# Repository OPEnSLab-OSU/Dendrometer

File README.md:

<p align="center">
    
  </a>
</p>

<h3 align="center">Dendrometer</h3>

## Introduction
The Dendrometer is an ongoing project that strives to enable ecological researchers and/or care-takers of grape plants to be able to effectively measure diurnal fluctuations in grape vines. Such information can be crucial for producing market-ideal grapes, as the shrinkage and growth of the vines are important indicators of when the plant is in need of water. Learn more about the design and outcomes on our <a href="https://github.com/OPEnSLab-OSU/OPEnS-Lab-Home/wiki/Dendrometer">Dendrometer Lab Wiki</a>. 

## Key Features
  - Data is collected and written to a SD card every 15 minutes, allowing the system to operate for long durations without human intervention
  - Devices can wirelessly report data back to a remote server by communicating with an internet-connected "hub" device
  - Magnetic encoder ([AS5311](https://ams.com/documents/20143/36005/AS5311_DS000200_2-00.pdf)) has a resolution of ~488nm with an extremely low temperature dependency (ideal for outdoor use)
  - Integration with [Loom](https://github.com/OPEnSLab-OSU/Loom-V4), which will allow this device to support plug-and-play functionalities with integrated sensors

## Directory 
### PCB: 
Printed circuit board (PCB) design files for the nodes. 
### src: 
Contains all of the code used on the dendrometer.
LoRa: Contains the source code for the node sensors and the LTE hub. This uses LoRa batch uploading which will upload all of the collected data at set intervals.
LoRa Non Batch: Contains the source code for the node sensors and the LTE hub. This will only upload ONE packet of data at set intervals. All of the data is still saved on SD card.
WiFi: Contains the source code for the WiFi connected nodes.

## Relevant Documents
* [User Manual](https://docs.google.com/document/d/1OHKa2jYamG2kPEfxrQMzi3MNHZGgkPIG/)
* [HardwareX Paper](https://www.sciencedirect.com/science/article/pii/S246806722100078X)
* [Troubleshooting Guide](https://docs.google.com/document/d/1E4zUMmSh5PVmP7RXUqQrh7S9IGuxQKPj5EQ5KcT2HYE/edit?usp=sharing)
* [Mechanical Assembly Guide](https://docs.google.com/document/d/1LzM_XnqVP9GkIqY2_pnTvdrFFe5u78ZPXJizvT70y4o/edit?usp=sharing)
* [Electronics Assembly Guide](https://docs.google.com/document/d/1BaNuNSJrL86lxKixB8chgZGySgj0bhYSMtVzJu6EDW4/edit?usp=sharing)
* [MongoDB Dashboard Guide](https://docs.google.com/document/d/1PlT9hrC62OXXhL8AD17e3FiPCwlHFJaZIvXCRnmihIE/edit?usp=sharing)
* [Installation Guide (Outdated)](https://docs.google.com/document/d/1GR2qeMWASApCwk-RbZwvsvWmB1qEz0QU8RcxwjgoDQY/edit?usp=sharing)

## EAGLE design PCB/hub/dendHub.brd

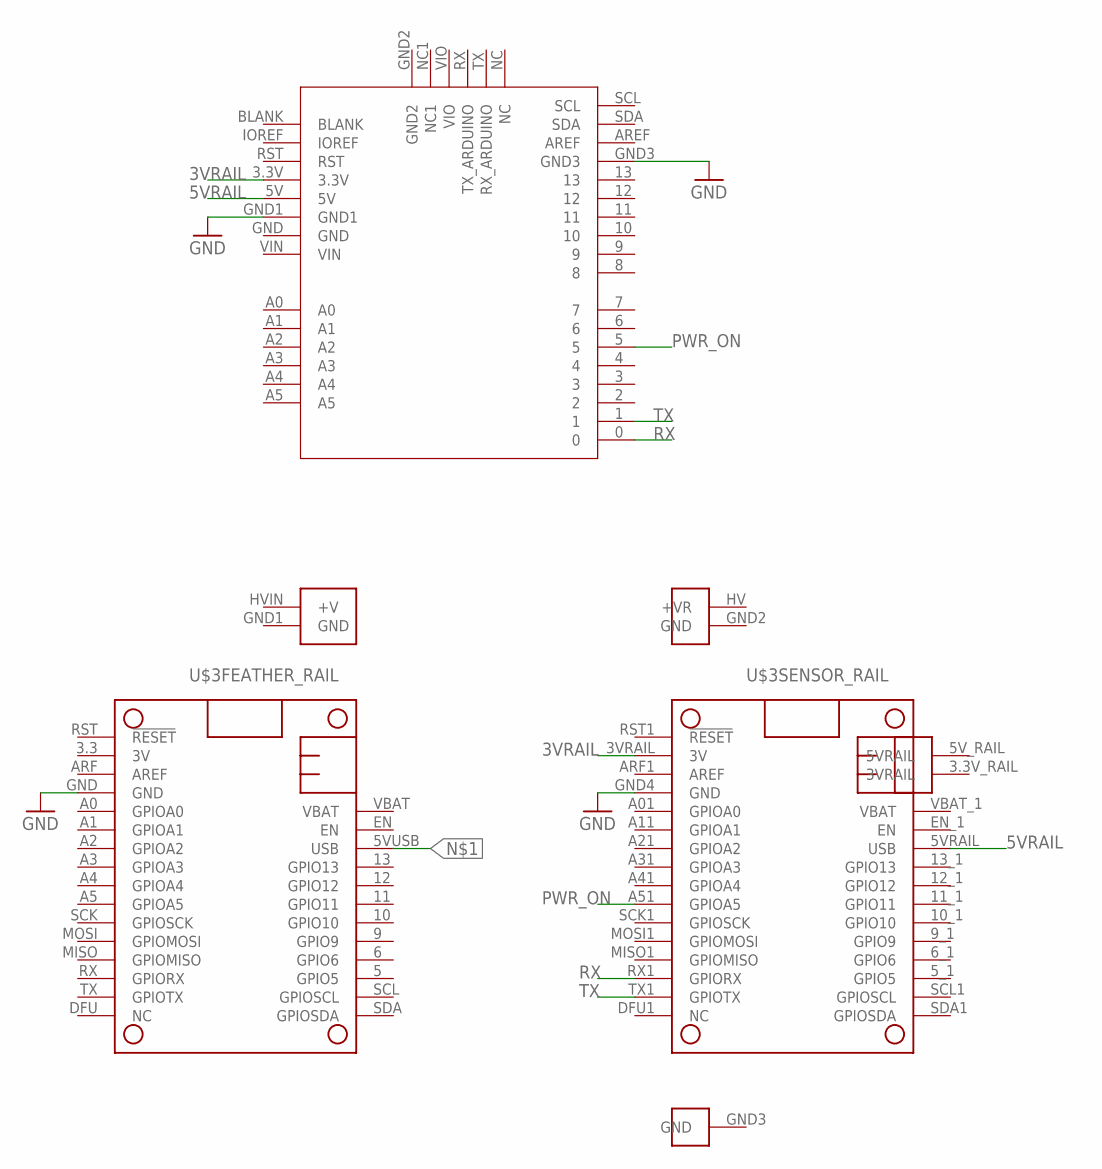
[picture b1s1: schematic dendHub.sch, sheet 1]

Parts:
U$1: LTE_BOARD; LTE_BOARD_FOOTPRINT
U$3: HYPNOS_V3

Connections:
3VRAIL: U$1.3.3V, U$3.3VRAIL (3V)
5VRAIL: U$1.5V, U$3.5VRAIL (USB)
GND: U$1.GND1, U$1.GND3, U$3.GND, U$3.GND4 (GND); also elsewhere on the board
unnamed 3: U$3.5VUSB (USB); also elsewhere on the board
PWR_ON: U$1.5, U$3.A51 (GPIOA5)
RX: U$1.0, U$3.RX1 (GPIORX)
TX: U$1.1, U$3.TX1 (GPIOTX)

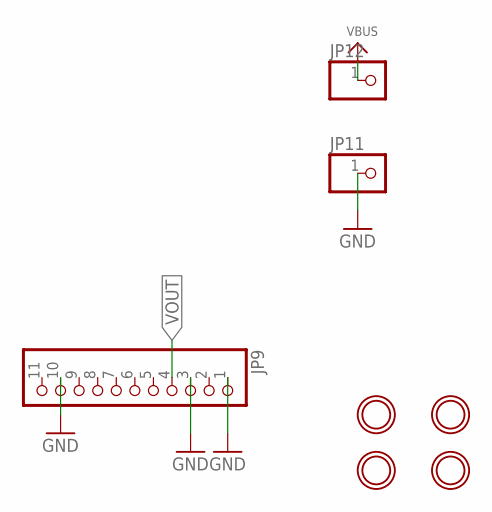
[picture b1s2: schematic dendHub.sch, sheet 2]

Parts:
JP9: HEADER-1X1176MIL; 1X11_ROUND_76
JP11, JP12: HEADER-1X1; 1X01_OVAL
U$45, U$46, U$47, U$48: MOUNTINGHOLE2.5; MOUNTINGHOLE_2.5_PLATED

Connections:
GND: JP9.1, JP9.3, JP9.10, JP11.1; also elsewhere on the board
VBUS: JP12.1
VOUT: JP9.4; also elsewhere on the board

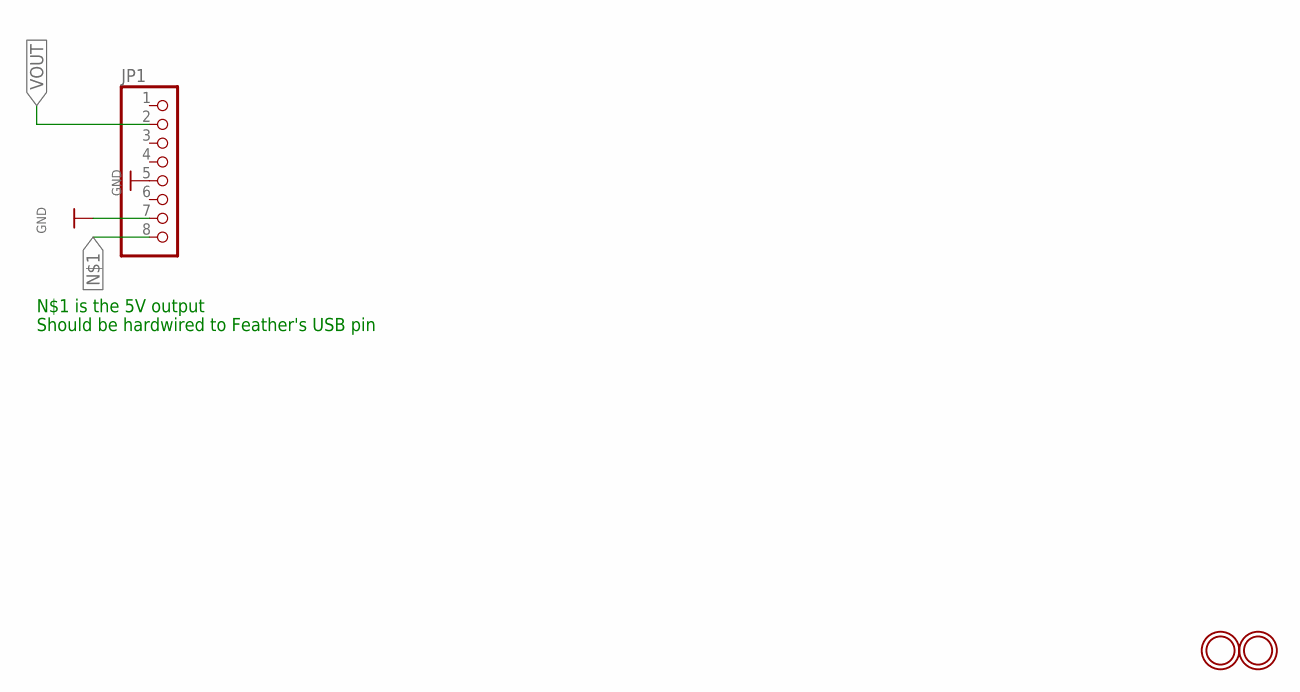
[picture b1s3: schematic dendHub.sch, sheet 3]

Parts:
JP1: HEADER-1X8ROUND; 1X08_ROUND
U$56, U$57: MOUNTINGHOLE2.5; MOUNTINGHOLE_2.5_PLATED

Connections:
GND: JP1.5, JP1.7; also elsewhere on the board
unnamed 3: JP1.8; also elsewhere on the board
VOUT: JP1.2; also elsewhere on the board

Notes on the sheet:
N$1 is the 5V output
Should be hardwired to Feather's USB pin

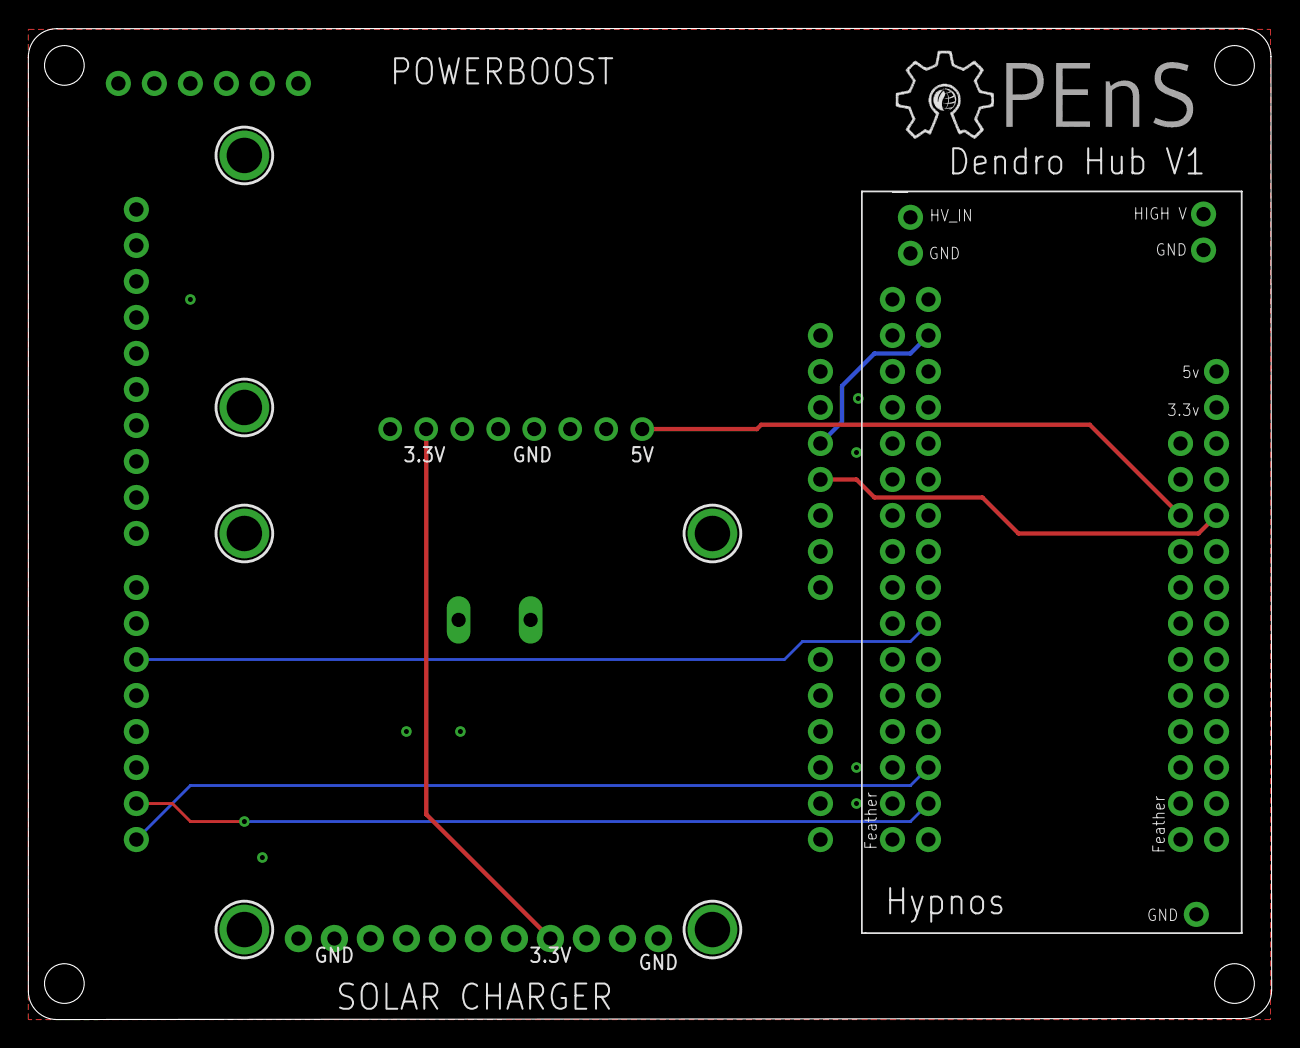
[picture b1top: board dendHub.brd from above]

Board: 2 copper layers, 87.7 x 69.9 mm, 13 parts (1 on the bottom side), 8 nets.

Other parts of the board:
U$2: OPENS-LOGO

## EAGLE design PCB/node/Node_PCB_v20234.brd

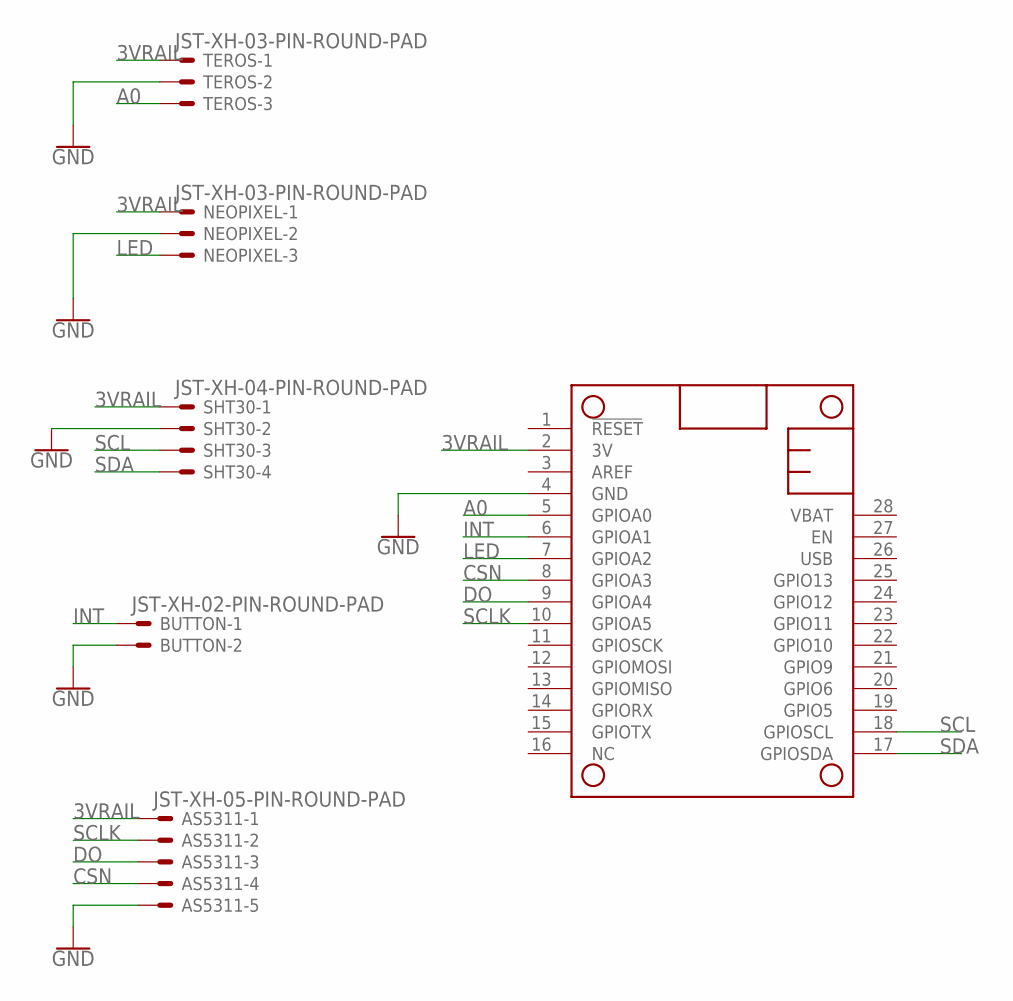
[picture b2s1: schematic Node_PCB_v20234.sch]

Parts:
AS5311: JST-XH-05-PIN-ROUND-PAD; JST-XH-05-PACKAGE-ROUND-PAD
BUTTON: JST-XH-02-PIN-ROUND-PAD; JST-XH-02-PACKAGE-ROUND-PAD
MS1: FEATHERWING
NEOPIXEL: JST-XH-03-PIN-ROUND-PAD; JST-XH-03-PACKAGE-ROUND-PAD
SHT30: JST-XH-04-PIN-ROUND-PAD; JST-XH-04-PACKAGE-ROUND-PAD
TEROS: JST-XH-03-PIN-ROUND-PAD; JST-XH-03-PACKAGE-ROUND-PAD

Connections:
3VRAIL: AS5311.1, MS1.2 (3V), NEOPIXEL.1, SHT30.1, TEROS.1
A0: MS1.5 (GPIOA0), TEROS.3
CSN: AS5311.4, MS1.8 (GPIOA3)
DO: AS5311.3, MS1.9 (GPIOA4)
GND: AS5311.5, BUTTON.2, MS1.4 (GND), NEOPIXEL.2, SHT30.2, TEROS.2
INT: BUTTON.1, MS1.6 (GPIOA1)
LED: MS1.7 (GPIOA2), NEOPIXEL.3
SCL: MS1.18 (GPIOSCL), SHT30.3
SCLK: AS5311.2, MS1.10 (GPIOA5)
SDA: MS1.17 (GPIOSDA), SHT30.4

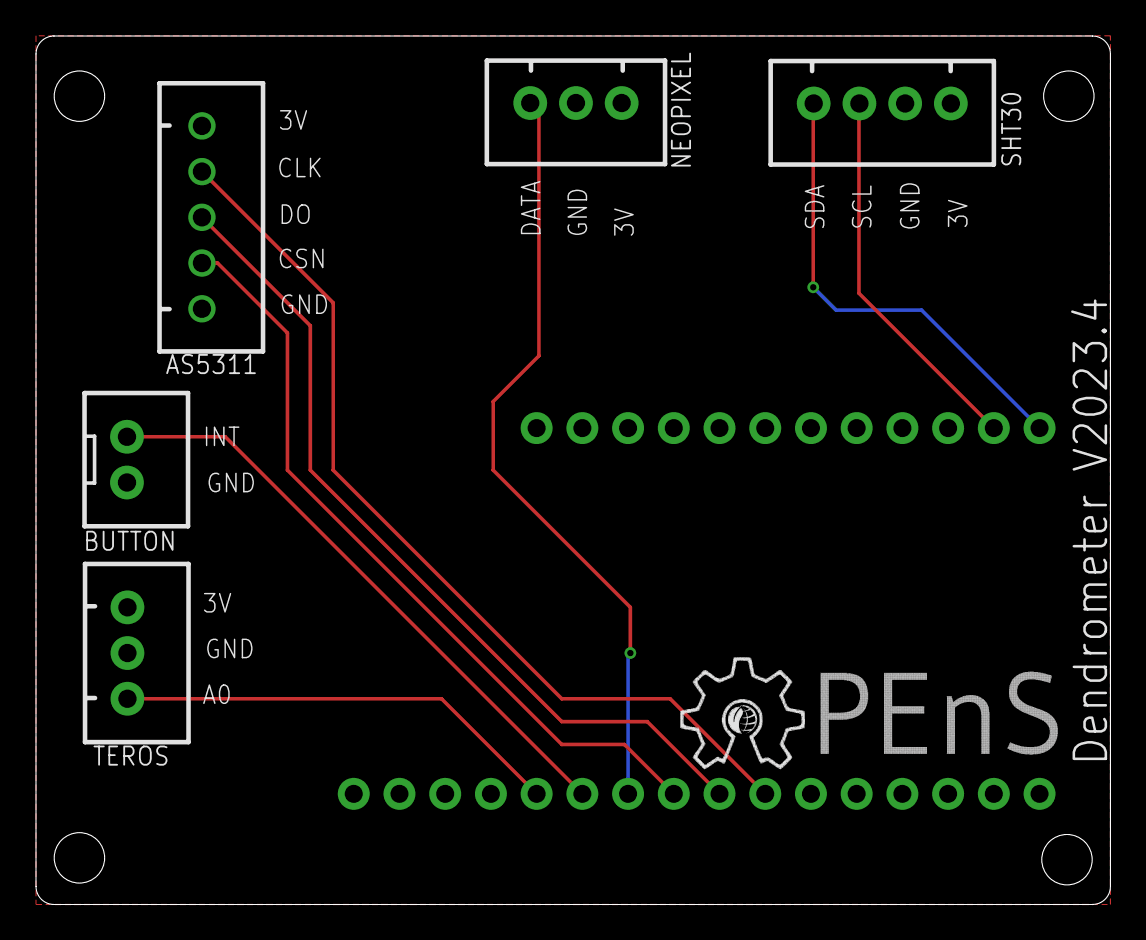
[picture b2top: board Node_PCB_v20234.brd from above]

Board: 2 copper layers, 59.7 x 48.2 mm, 7 parts (0 on the bottom side), 10 nets.

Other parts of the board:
U$1: OPENS-LOGO

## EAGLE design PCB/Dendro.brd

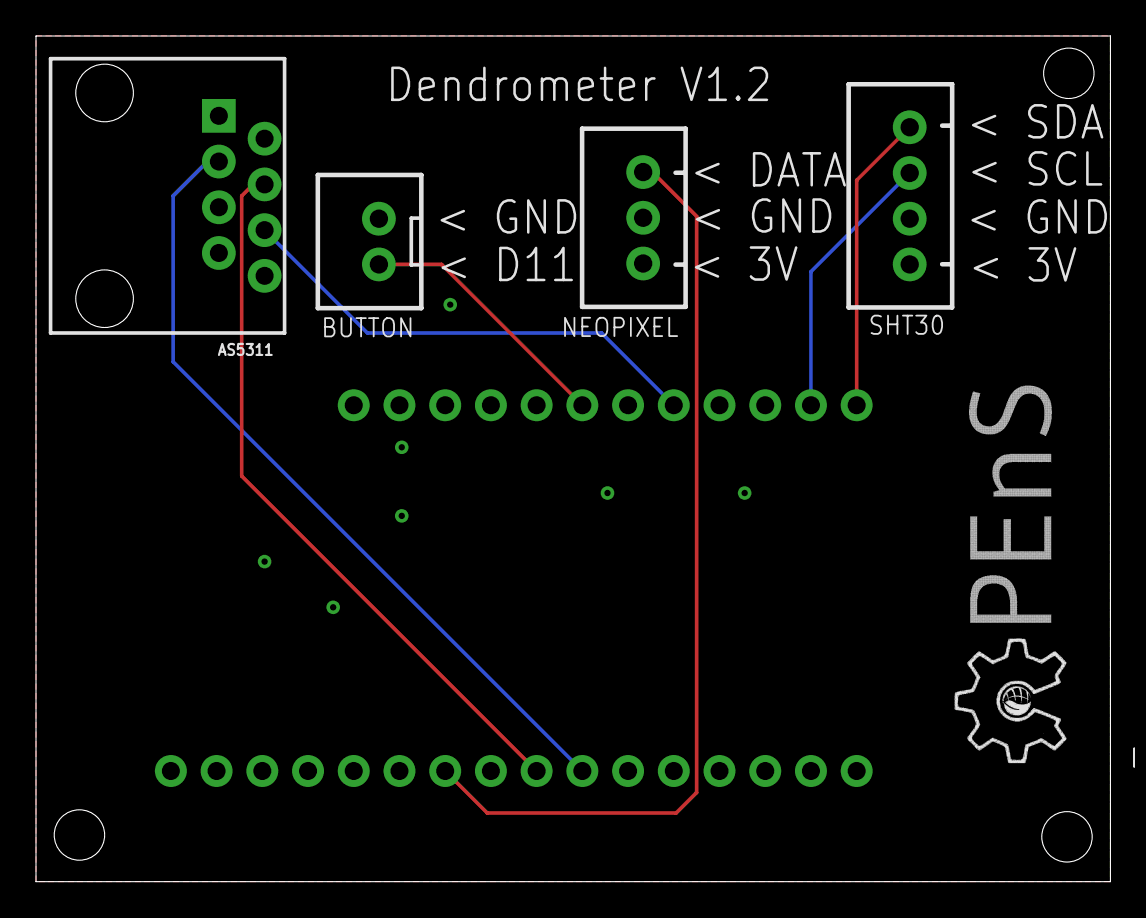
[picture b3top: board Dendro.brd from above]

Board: 2 copper layers, 59.7 x 47.0 mm, 6 parts (0 on the bottom side), 9 nets.

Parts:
AS5311: RJ45; RJ45-8
BUTTON: JST-XH-02-PIN-ROUND-PAD; JST-XH-02-PACKAGE-ROUND-PAD
MS1: FEATHERWING
NEOPIXEL: JST-XH-03-PIN-ROUND-PAD; JST-XH-03-PACKAGE-ROUND-PAD
SHT30: JST-XH-04-PIN-ROUND-PAD; JST-XH-04-PACKAGE-ROUND-PAD
U$1: OPENS-LOGO

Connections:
3VRAIL: AS5311.1, AS5311.2, MS1.2, NEOPIXEL.1, SHT30.1
A2: MS1.7, NEOPIXEL.3
CSN: AS5311.6, MS1.21
D11: BUTTON.1, MS1.23
DO: AS5311.4, MS1.9
GND: AS5311.5, BUTTON.2, MS1.4, NEOPIXEL.2, SHT30.2
SCL: MS1.18, SHT30.3
SCLK: AS5311.3, MS1.10
SDA: MS1.17, SHT30.4

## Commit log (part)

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2019-07-12 Create Linear_Slide_4.ino
    Reads sensor data and stores on micro SD using Adalogger and RTC
2019-08-22 SHT and Voltage ref
    Added sht sensor, lm4040 voltage reference
2019-11-04 image and image folder
2019-11-05 another picture
2019-11-05 picture and drawing
2019-11-05 graph
2019-11-25 Added AS5311, AS5311 example, and updates potentiometer
2019-11-25 Most recent linear potentiometer code
2019-11-25 Loom
2019-12-09 Create test
2019-12-21 Connected to Wifi
2019-12-22 Successfully got PWM
2019-12-24 Implemented basic HTTP Functionality
2019-12-26 Successfully made PUT request
2019-12-29 Implemented basic functionality of writing
2019-12-29 Implemented vector functionality for update
2019-12-30 Implemented functionality of refresh
2019-12-30 Added example of GSheets usage
2019-12-30 Removed extra delay
2020-01-07 Removed extra files
2020-01-13 Integrated WiFi onto Feather M0
2020-01-27 Before integrating Serial
2020-01-29 Integrated Serial
2020-01-29 Attempt to fix wifi and added 16 loop
2020-01-30 Added Wifi Disconnect statement
2020-02-24 Successfully sensed rollover
2020-02-25 Displacement algorithm v1
2020-02-26 Remove .DS_STORE
2020-02-26 File Reorg
2020-03-05 Integrated basic Loom functionality, need to parse data
2020-03-10 Added Loom SD and refactored AS5331
2020-03-11 Refactored Code into header files and renamed file typo
2020-03-12 Integrated SD card functionality
2020-04-23 Added mechanical test code
2020-06-07 Push code for summer mechanical testing
2020-07-20 Renamed Hypnos variables
2020-08-11 Updated summer prototyping code
2020-08-30 Updated summer code testing
2020-08-30 Updated code for summer testing
2020-09-07 Added error checking for magnet position
2020-09-22 Changed time between readings to 15 minutes
2020-09-23 Added temporary magnet checker during setup
2020-10-02 Magnet checker during setup implemented
2020-10-10 Neopixel added, more specific error messages
2020-10-10 More detailed error messages for testing
2020-10-12 Warm up time added for AS5311, Neopixel blink
2020-11-07 Create STLfiles
2020-11-10 Testing New Schematic Editor
2020-11-10 Updated Schematic for AGU
2020-11-13 Battery levels recorded
2020-12-06 Dendrometer PCB V1
2020-12-06 PCB PDFs
2020-12-06 Rename DendroSchem.brd to Dendro.brd
2020-12-06 Rename DendroSchem.sch to Dendro.sch
2020-12-11 Added RTC PST timing and decreased LED time
2021-01-07 Added interrupt button
2021-01-12 Create dwgs
2021-01-12 Create boop
2021-01-12 Create go
2021-01-12 Create kip
2021-01-24 Zenodo file uploaded
2021-01-27 Cleaned up code
2021-01-29 Neopixel Interrupt
2021-01-30 Neopixel indicator
2021-01-30 RTC Update
2021-01-30 Neopixel Update
2021-01-31 Fixed Loom power rail bug
2021-01-31 Fixed OCF Error
2021-02-17 Added VPD calculation
2021-02-20 Implemented functionality of LoRa + Dendro
2021-02-21 Dendro PCB V1.1
2021-03-05 Fixed LoRa + Loom interaction
2021-03-09 Added Lora Files
2021-03-09 Added code for LoRa + Dendrometer Testing
2021-03-10 Added LoRa changes for field tests
2021-03-11 Added name module to allow for isolated Gsheet publishing
2021-04-02 New LoRa Test Scripts
2021-04-02 Added Sleep and RTC Implementation
2021-04-14 LoRa deployment code
2021-04-14 Removed batch send, Added Retries
    The Node will now retry the amount of times specified by "MAX_RETRIES" before going into sleep mode.
2021-04-17 Log to SD on hub
2021-04-17 Ethernet module added
2021-04-21 Changed LoRa send
    Made the LoRa send have max retries and max timeout.
2021-05-04 Fixed Google Sheet bug, removed unnecessary lines
2021-05-06 Google Sheets Test Code
2021-05-06 Revert "Google Sheets Test Code"
    This reverts commit 31800c380b1dfee6701abbce808143c6da912e60.
2021-05-06 Deployment Test Code
2021-05-19 Updated deployment testing code
2021-06-25 Updated code + PCB for summer deployments
2021-08-05 Dendrometer V1.2
    Updated PCBs for node and hub as well as includes code for both Ethernet and LTE telemetry
2021-11-04 Summer 2022 Deployment Prep
    Updated PCBs and code, includes Loom V3 and HypnosV3.3 changes
2021-12-28 Summer 2022 Deployment
    Removed BatchSD due to Loom V3 issues with publishing
2022-01-06 Updated comments
2022-01-06 Code spacing
2022-01-13 Logs whether button was pressed
2022-01-14 Updated comments, log whether system woke up from button or not
2022-01-15 Unnecessary delay
2022-01-27 Updated comments for code
2022-02-16 Added LoRa transmission every 4 hours instead of every hour
2022-03-09 SHT30 measures outside of Loom, LoRa transmits on 2nd packet
2022-03-21 Added AS5311 back into Loom
2022-03-31 Updated LB farm code
2022-04-01 LoRa transmits every 16 packets
2022-05-19 Added SHT back in from Loom
2022-09-09 File cleanup
2022-11-01 wip (compiles)
2022-11-03 remove outdated mechanical drawings from future commits
2022-12-02 tweak magnet sensor code
2022-12-16 testing changes
2023-01-01 Fix button interrupt, fix LED color encoding
2023-01-20 add comments make constants more obvious add #define statment that disables the radio wip overflow/displacement calculation experimental magnet sensor checking code add some testing code for looking 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
2023-01-20 check parity bit
2023-01-24 add micrometer displacement calculation
2023-01-24 I hate arduino
2023-02-01 magnet strength
2023-02-09 refactor. everything sems to be working
2023-02-13 remove unused #include
2023-02-20 code review
2023-02-22 small refactor
2023-02-28 implement wifi connectivity
2023-03-01 tested with loom 297dc9b
2023-03-17 note LB pin numbers
2023-03-19 working on new batch of devices
2023-03-19 add setrtc(), improve effieciency of data upload
2023-03-22 finalize
2023-03-22 change database name
2023-03-23 add connection credentials
2023-03-23 database name
2023-04-08 generalize
2023-04-28 Fix initial position issue
2023-05-07 SD credentials for hub
2023-05-15 add RTC setup and battery voltage reporting to hub
2023-05-15 update PCB files
2023-05-15 add Teros10 sensor
2023-06-09 switch back to GRB leds
2023-06-09 change log name
2023-08-02 Bug report template
2023-08-02 custom issue template
2023-08-02 Feature Request
2023-08-02 Implementation Request
2023-08-02 Project Specification
2023-09-26 Add blank project parameter to mqtt credentials
2023-11-06 Update comments
2023-12-05 Dendrometer Status Code
    Code written by Dajeong Kim from UBC team. This code connects to MongoDB and sends email reports about alignment, battery status, and scatter plots of collected data
2023-12-05 Dendrometer Status Code
2023-12-05 Revert "Dendrometer Status Code "
    This reverts commit ed0454ab28571e7ed4edb49901d79567d0fab41a.
2023-12-05 Dendrometer Status Code
    This code was written by Dajeong Kim from UBC team. This code connects to MongoDB and sends email reports of alignment, battery status, and data point plots
2023-12-05 Create Working Data Cleaning Code
    This data-cleaning code was developed by Dragomira Zheleva. The code cleans the data by extracting outliers from imported dendrometer data using interquartile ranges. The current interquartile ranges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
2023-12-05 Create CSV Combining Code
    This code was written by Jordan Porter and combines multiple CSV files created by a dendrometer
2023-12-08 Revert "Delete Data Cleaning directory"
    This reverts commit 9cfdc0692fabcb78472d3521707d882c2014f99d.
2023-12-08 Delete Data Cleaning/Working Data Cleaning Code
    removed Dragomira data cleaning code
2023-12-11 Use raw position for displacement rather than filtered average to avoid outliers
2023-12-19 power cycle lte modem if no connection to internet
2024-01-21 Updated instances of Loom_MQTT to Loom_MongoDB for use with Loom 4.6
2024-01-21 Added NTP sync for internet connected devices
2024-01-24 Initial lora batch and lte batch upload
2024-02-03 attempt null packet fix (not working)
2024-02-03 removed time sync for hub
2024-02-16 Finalized LoRa Batch for deployment
2024-03-04 fix wifi NTP
2024-03-06 fixed accidentally deleting hypnos enable
2024-03-12 minor changes. (remove connection check)
2025-01-11 remove .getclient()
2025-04-09 Create troubleshooting
2025-04-09 Rename troubleshooting to troubleshooting.md
2025-04-25 Add hypnosconfig.json
2025-04-25 add hypnosconfig.json to lora non batch
2025-04-29 separated source code into separate for LoRa and WiFi devices
2025-04-29 remove unnecessary dependency
2025-10-08 Added parallel power board PCB gerber
2025-11-06 remove arduino_secrets
2025-11-08 generic credentials
2025-11-08 update gitignore
2026-03-07 Updated git ignore
2026-03-07 Fixed nonbatch code
2026-03-14 Initial heartbeat code added
2026-03-18 Non batch LoRa naming fix
2026-03-18 Fixed non batch transmit node code
2026-04-05 Commented out LoRa functionality
2026-04-05 fixed
2026-04-21 Updated naming
2026-04-21 Added handshake implementation
2026-04-28 Comments plus removed redundant heartbeat code in hub file
2026-04-28 Changed receive to correctly proxy
2026-04-28 "fixed naming"
2026-04-29 "increased time"
2026-05-12 Added mongoDB test files
2026-05-12 Fixed hub naming mongo upload
2026-05-14 added heartbeat functionality, added heartbeat add data to as5311 class
2026-05-15 Added more test code, not currently working
2026-05-19 added heartbeat hub logging fix

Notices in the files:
parts and their libraries:
SparkFun-Connectors: Licensing: Creative Commons ShareAlike 4.0 International - https://creativecommons.org/licenses/by-sa/4.0
